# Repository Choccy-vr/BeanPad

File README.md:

# BeanPad

A modular magnetic macro pad. Use many different modules to make the macro pad of your dreams. Modify the macros.json for a custom keymap.

I built this originally as a buffer for my main project but it has since taken over it. The idea came from other snap-fit modular systems and thought it was cool. I originally was just going to make a hack pad but it quickly grew into this.
I also built this in case my other project doesn't get finished in time for undercity.
## Images

### PCB

### Case

### Firmware (Really nothing to see here)

## 
|Item:             |Quanity: (If Items come in sets amount of sets)|Source:                                                                                                                                                                                                                                                                                                                                                                                                                                   |Cost:  |Total                                |
|------------------|-----------------------------------------------|------------------------------------------------------------------------------------------------------------------------------------------------------------------------------------------------------------------------------------------------------------------------------------------------------------------------------------------------------------------------------------------------------------------------------------------|-------|-------------------------------------|
|Screws            |1(50pcs)                                       |https://www.aliexpress.us/item/3256802339245383.html?spm=a2g0o.cart.0.0.7a1938daQ49wN7&mp=1&pdp_npi=5%40dis%21USD%21USD%201.46%21USD%201.41%21%21USD%201.41%21%21%21%402103273e17501073692076879ef915%2112000021000038128%21ct%21US%213108417632%21%211%210&_gl=1*ga8tl1*_gcl_au*NDM2NDExMDYwLjE3NDk1NzAxOTM.*_ga*Nzg5NDk5ODkzLjE3NTAxMDU1ODU.*_ga_VED1YSGNC7*czE3NTAxMDU1ODQkbzEkZzEkdDE3NTAxMDczNzAkajUxJGwwJGgw&gatewayAdapt=glo2usa   |$1.50  |                                     |
|Heat Set Inserts  |1(50pcs)                                       |https://www.aliexpress.us/item/3256807466816961.html?spm=a2g0o.cart.0.0.7a1938daQ49wN7&mp=1&pdp_npi=5%40dis%21USD%21USD%202.02%21USD%201.93%21%21USD%201.93%21%21%21%402103273e17501073692076879ef915%2112000041667111488%21ct%21US%213108417632%21%211%210&_gl=1*ga8tl1*_gcl_au*NDM2NDExMDYwLjE3NDk1NzAxOTM.*_ga*Nzg5NDk5ODkzLjE3NTAxMDU1ODU.*_ga_VED1YSGNC7*czE3NTAxMDU1ODQkbzEkZzEkdDE3NTAxMDczNzAkajUxJGwwJGgw&gatewayAdapt=glo2usa   |$2     |                                     |
|Diodes            |1(100pcs)                                      |https://www.aliexpress.us/item/2255799955957794.html?spm=a2g0o.cart.0.0.7a1938daQ49wN7&mp=1&pdp_npi=5%40dis%21USD%21USD%201.42%21USD%201.42%21%21USD%201.39%21%21%21%402103273e17501073692076879ef915%2110000000428321629%21ct%21US%213108417632%21%211%210&_gl=1*ga8tl1*_gcl_au*NDM2NDExMDYwLjE3NDk1NzAxOTM.*_ga*Nzg5NDk5ODkzLjE3NTAxMDU1ODU.*_ga_VED1YSGNC7*czE3NTAxMDU1ODQkbzEkZzEkdDE3NTAxMDczNzAkajUxJGwwJGgw&gatewayAdapt=glo2usa   |$1     |                                     |
|Cherry MX Switches|1(30pcs)                                       |https://www.aliexpress.us/item/3256806069646359.html?spm=a2g0o.cart.0.0.7a1938daQ49wN7&mp=1&pdp_npi=5%40dis%21USD%21USD%2019.50%21USD%2018.55%21%21USD%2018.55%21%21%21%402103273e17501073692076879ef915%2112000036489552474%21ct%21US%213108417632%21%211%210&_gl=1*xvozit*_gcl_au*NDM2NDExMDYwLjE3NDk1NzAxOTM.*_ga*Nzg5NDk5ODkzLjE3NTAxMDU1ODU.*_ga_VED1YSGNC7*czE3NTAxMDU1ODQkbzEkZzEkdDE3NTAxMDczNzckajQ0JGwwJGgw&gatewayAdapt=glo2usa|$19    |                                     |
|Rotary Encoders   |2                                              |https://www.aliexpress.us/item/3256805010555504.html?spm=a2g0o.cart.0.0.7a1938daQ49wN7&mp=1&pdp_npi=5%40dis%21USD%21USD%201.59%21USD%201.57%21%21USD%201.57%21%21%21%402103273e17501073692076879ef915%2112000032095591035%21ct%21US%213108417632%21%212%210&_gl=1*b3zsk7*_gcl_au*NDM2NDExMDYwLjE3NDk1NzAxOTM.*_ga*Nzg5NDk5ODkzLjE3NTAxMDU1ODU.*_ga_VED1YSGNC7*czE3NTAxMDU1ODQkbzEkZzEkdDE3NTAxMDczNzgkajQzJGwwJGgw&gatewayAdapt=glo2usa   |$3     |                                     |
|KeyCaps           |2(24pcs)                                       |https://www.aliexpress.us/item/3256802719703092.html?spm=a2g0o.cart.0.0.7a1938daQ49wN7&mp=1&pdp_npi=5%40dis%21USD%21USD%204.15%21USD%203.86%21%21USD%203.62%21%21%21%402103273e17501073692076879ef915%2112000025975791590%21ct%21US%213108417632%21%212%210&_gl=1*b3zsk7*_gcl_au*NDM2NDExMDYwLjE3NDk1NzAxOTM.*_ga*Nzg5NDk5ODkzLjE3NTAxMDU1ODU.*_ga_VED1YSGNC7*czE3NTAxMDU1ODQkbzEkZzEkdDE3NTAxMDczNzgkajQzJGwwJGgw&gatewayAdapt=glo2usa   |$7     |                                     |
|Pogo Connectors   |3(9 pairs)                                     |https://www.aliexpress.us/item/3256806345459324.html?spm=a2g0o.detail.0.0.9f08fUkJfUkJyL&mp=1&pdp_npi=5%40dis%21USD%21USD%206.80%21USD%206.80%21%21USD%206.80%21%21%21%402103273e17501073828027372ef915%2112000045728213793%21ct%21US%213108417632%21%213%210&_gl=1*1iabbhw*_gcl_au*NDM2NDExMDYwLjE3NDk1NzAxOTM.*_ga*Nzg5NDk5ODkzLjE3NTAxMDU1ODU.*_ga_VED1YSGNC7*czE3NTAxMDU1ODQkbzEkZzEkdDE3NTAxMDc3MDAkajE2JGwwJGgw&gatewayAdapt=glo2usa|$21    |                                     |
|Soldering Iron    |1                                              |https://www.aliexpress.us/item/3256806823950124.html?spm=a2g0o.cart.0.0.7a1938daQ49wN7&mp=1&pdp_npi=5%40dis%21USD%21USD%2019.24%21USD%207.89%21%21USD%207.89%21%21%21%402103273e17501073692076879ef915%2112000039050811400%21ct%21US%213108417632%21%211%210&_gl=1*y42j40*_gcl_au*NDM2NDExMDYwLjE3NDk1NzAxOTM.*_ga*Nzg5NDk5ODkzLjE3NTAxMDU1ODU.*_ga_VED1YSGNC7*czE3NTAxMDU1ODQkbzEkZzEkdDE3NTAxMDczODEkajQwJGwwJGgw&gatewayAdapt=glo2usa  |$8     |                                     |
|XIAO Rp2040s      |2 (6pcs)                                       |https://www.seeedstudio.com/Seeed-Studio-XIAO-RP2040-3PCS-p-5942.html                                                                                                                                                                                                                                                                                                                                                                     |$27    |                                     |
|PCBs              |4                                              |https://www.pcbway.com/                                                                                                                                                                                                                                                                                                                                                                                                                   |$47.84 |                                     |
|Total             |                                               |                                                                                                                                                                                                                                                                                                                                                                                                                                          |       |$148.23 (Includes Shipping and Taxes)|

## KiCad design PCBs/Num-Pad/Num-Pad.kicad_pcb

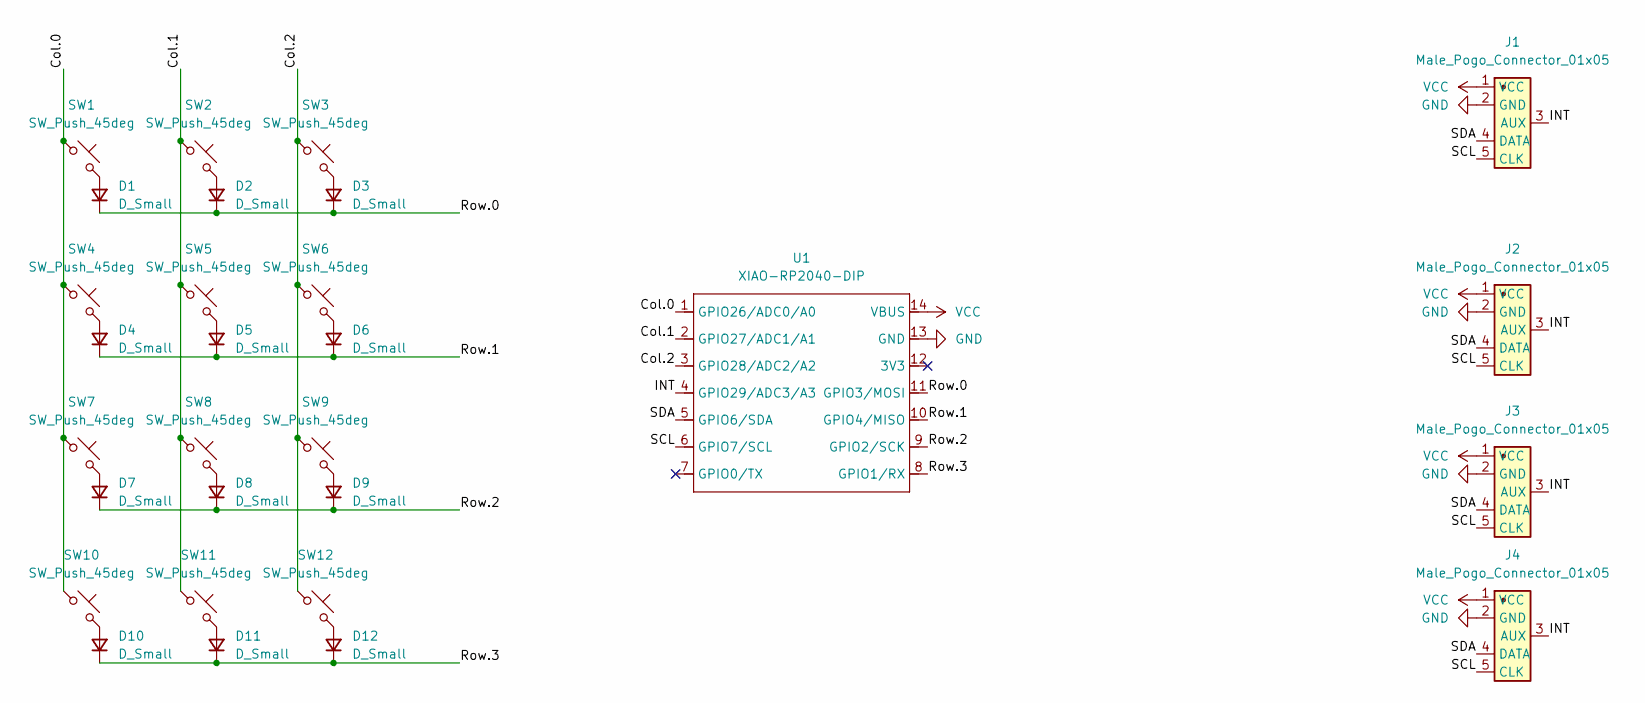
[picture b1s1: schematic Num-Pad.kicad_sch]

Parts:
D1, D2, D3, D4, D5, D6, D7, D8, D9, D10, D11, D12: D_Small; D_DO-35_SOD27_P7.62mm_Horizontal
J1, J2, J3, J4: Male_Pogo_Connector_01x05; PinHeader_1x05_P2.54mm_Vertical
SW1, SW2, SW3, SW4, SW5, SW6, SW7, SW8, SW9, SW10, SW11, SW12: SW_Push_45deg; SW_Cherry_MX_1.00u_PCB
U1: XIAO-RP2040-DIP

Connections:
/Col.0: SW1.1, SW4.1, SW7.1, SW10.1, U1.1 (GPIO26/ADC0/A0)
/Col.1: SW2.1, SW5.1, SW8.1, SW11.1, U1.2 (GPIO27/ADC1/A1)
/Col.2: SW3.1, SW6.1, SW9.1, SW12.1, U1.3 (GPIO28/ADC2/A2)
/INT: J1.3 (AUX), J2.3 (AUX), J3.3 (AUX), J4.3 (AUX), U1.4 (GPIO29/ADC3/A3)
/Row.0: D1.1 (K), D2.1 (K), D3.1 (K), U1.11 (GPIO3/MOSI)
/Row.1: D4.1 (K), D5.1 (K), D6.1 (K), U1.10 (GPIO4/MISO)
/Row.2: D7.1 (K), D8.1 (K), D9.1 (K), U1.9 (GPIO2/SCK)
/Row.3: D10.1 (K), D11.1 (K), D12.1 (K), U1.8 (GPIO1/RX)
/SCL: J1.5 (CLK), J2.5 (CLK), J3.5 (CLK), J4.5 (CLK), U1.6 (GPIO7/SCL)
/SDA: J1.4 (DATA), J2.4 (DATA), J3.4 (DATA), J4.4 (DATA), U1.5 (GPIO6/SDA)
GND: J1.2 (GND), J2.2 (GND), J3.2 (GND), J4.2 (GND), U1.13 (GND)
unnamed: D1.2 (A), SW1.2
unnamed: D2.2 (A), SW2.2
unnamed: D3.2 (A), SW3.2
unnamed: D4.2 (A), SW4.2
unnamed: D5.2 (A), SW5.2
unnamed: D6.2 (A), SW6.2
unnamed: D7.2 (A), SW7.2
unnamed: D8.2 (A), SW8.2
unnamed: D9.2 (A), SW9.2
unnamed: D10.2 (A), SW10.2
unnamed: D11.2 (A), SW11.2
unnamed: D12.2 (A), SW12.2
VCC: J1.1 (VCC), J2.1 (VCC), J3.1 (VCC), J4.1 (VCC), U1.14 (VBUS)

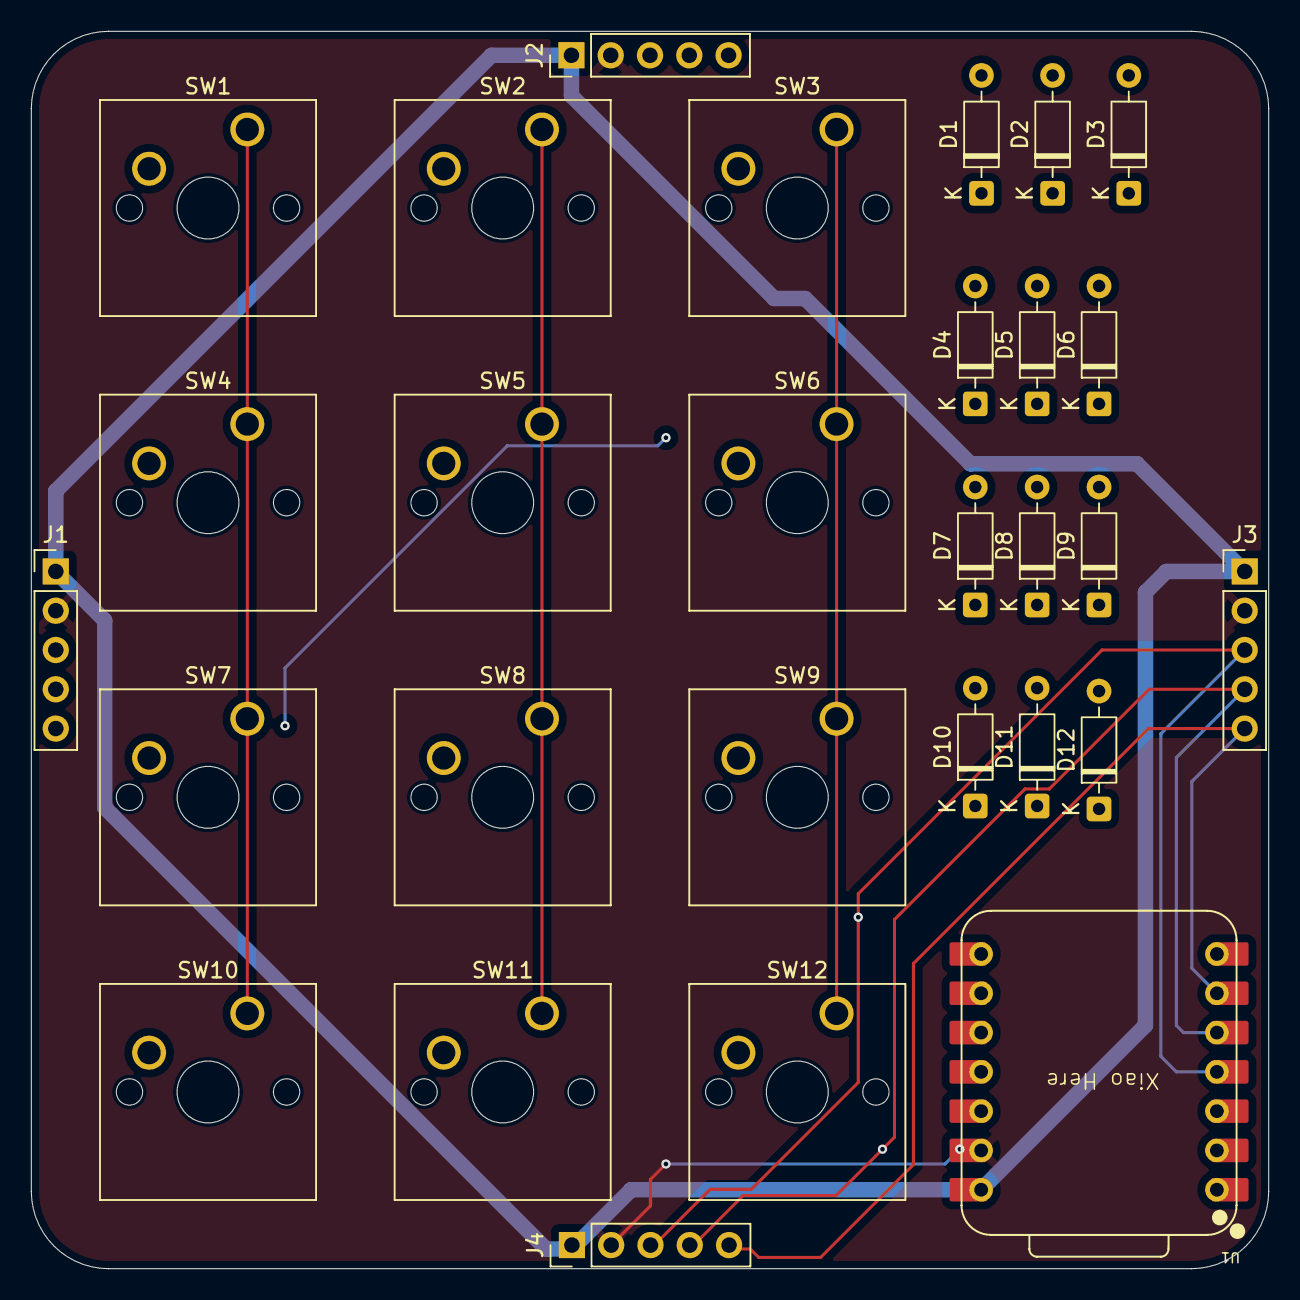
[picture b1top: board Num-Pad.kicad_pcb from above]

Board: 4 copper layers, 80.0 x 80.0 mm, 29 parts (0 on the bottom side), 24 nets.

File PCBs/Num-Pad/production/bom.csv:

Designator,Footprint,Quantity,Value,LCSC Part #
"D1, D10, D11, D12, D2, D3, D4, D5, D6, D7, D8, D9",D_DO-35_SOD27_P7.62mm_Horizontal,12,D_Small,
"J1, J2, J3, J4",PinHeader_1x05_P2.54mm_Vertical,4,Male_Pogo_Connector_01x05,
"SW1, SW10, SW11, SW12, SW2, SW3, SW4, SW5, SW6, SW7, SW8, SW9",SW_Cherry_MX_1.00u_PCB,12,SW_Push_45deg,
U1,XIAO-RP2040-DIP,1,XIAO-RP2040-DIP,

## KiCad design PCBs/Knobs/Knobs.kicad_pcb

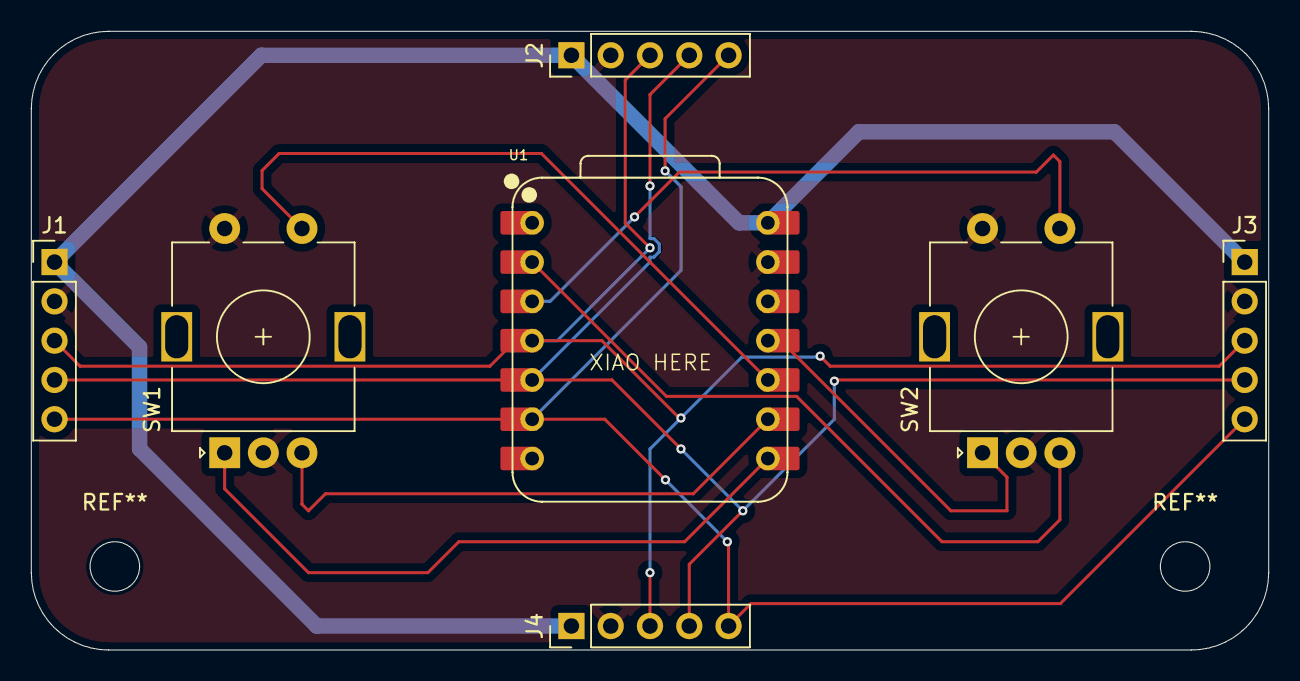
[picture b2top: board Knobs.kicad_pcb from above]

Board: 2 copper layers, 80.0 x 40.0 mm, 7 parts (0 on the bottom side), 11 nets.

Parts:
J1, J2, J3, J4: Male_Pogo_Connector_01x05; PinHeader_1x05_P2.54mm_Vertical
SW1, SW2: RotaryEncoder_Switch; RotaryEncoder_Alps_EC11E-Switch_Vertical_H20mm
U1: XIAO-RP2040-DIP

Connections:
/GPIO1: SW1.A, U1.8 (GPIO1/RX)
/GPIO2: SW1.B, U1.9 (GPIO2/SCK)
/GPIO3: SW2.A, U1.11 (GPIO3/MOSI)
/GPIO4: SW1.S1, U1.10 (GPIO4/MISO)
/GPIO27: SW2.B, U1.2 (GPIO27/ADC1/A1)
/GPIO28: SW2.S1, U1.3 (GPIO28/ADC2/A2)
/INT: J1.3 (AUX), J2.3 (AUX), J3.3 (AUX), J4.3 (AUX), U1.4 (GPIO29/ADC3/A3)
/SCL: J1.5 (CLK), J2.5 (CLK), J3.5 (CLK), J4.5 (CLK), U1.6 (GPIO7/SCL)
/SDA: J1.4 (DATA), J2.4 (DATA), J3.4 (DATA), J4.4 (DATA), U1.5 (GPIO6/SDA)
GND: J1.2 (GND), J2.2 (GND), J3.2 (GND), J4.2 (GND), SW1.C, SW1.S2, SW2.C, SW2.S2, U1.13 (GND)
VCC: J1.1 (VCC), J2.1 (VCC), J3.1 (VCC), J4.1 (VCC), U1.14 (VBUS)

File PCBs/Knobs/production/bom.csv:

Designator,Footprint,Quantity,Value,LCSC Part #
"J1, J2, J3, J4",PinHeader_1x05_P2.54mm_Vertical,4,Male_Pogo_Connector_01x05,
"SW1, SW2",RotaryEncoder_Alps_EC11E-Switch_Vertical_H20mm,2,RotaryEncoder_Switch,
U1,XIAO-RP2040-DIP,1,XIAO-RP2040-DIP,

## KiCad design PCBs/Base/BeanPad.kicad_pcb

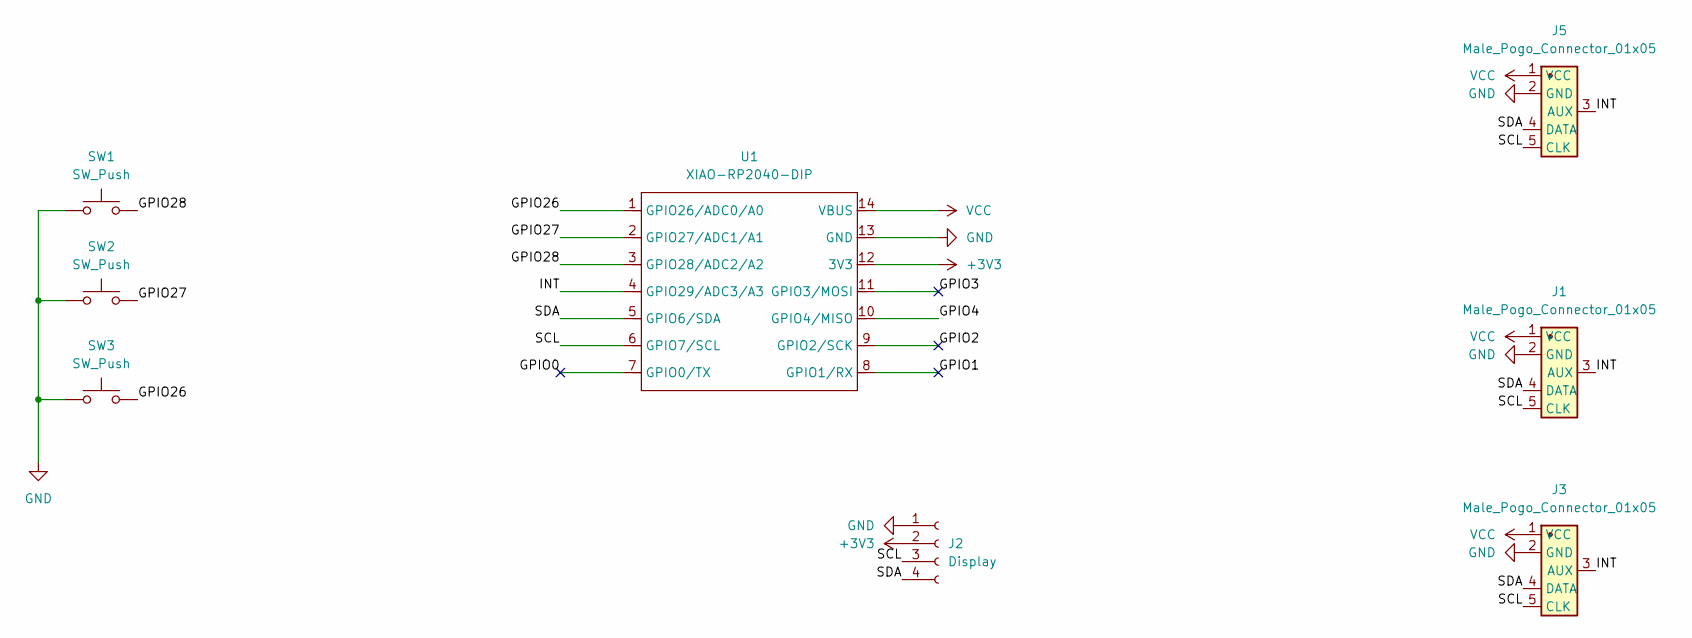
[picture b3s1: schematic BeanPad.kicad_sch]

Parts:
J1, J3, J5: Male_Pogo_Connector_01x05; PinHeader_1x05_P2.54mm_Vertical
J2: Display; SSD1306-0.91-OLED-4pin-128x32
SW1, SW2, SW3: SW_Push; SW_Cherry_MX_1.00u_PCB
U1: XIAO-RP2040-DIP

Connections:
+3V3: J2.2, U1.12 (3V3)
/GPIO0: U1.7 (GPIO0/TX)
/GPIO0_1: U1.7 (GPIO0/TX)
/GPIO1: U1.8 (GPIO1/RX)
/GPIO1_1: U1.8 (GPIO1/RX)
/GPIO2: U1.9 (GPIO2/SCK)
/GPIO2_1: U1.9 (GPIO2/SCK)
/GPIO3: U1.11 (GPIO3/MOSI)
/GPIO3_1: U1.11 (GPIO3/MOSI)
/GPIO4: U1.10 (GPIO4/MISO)
/GPIO26: SW3.2, U1.1 (GPIO26/ADC0/A0)
/GPIO27: SW2.2, U1.2 (GPIO27/ADC1/A1)
/GPIO28: SW1.2, U1.3 (GPIO28/ADC2/A2)
/INT: J1.3 (AUX), J3.3 (AUX), J5.3 (AUX), U1.4 (GPIO29/ADC3/A3)
/SCL: J1.5 (CLK), J2.3, J3.5 (CLK), J5.5 (CLK), U1.6 (GPIO7/SCL)
/SDA: J1.4 (DATA), J2.4, J3.4 (DATA), J5.4 (DATA), U1.5 (GPIO6/SDA)
GND: J1.2 (GND), J2.1, J3.2 (GND), J5.2 (GND), SW1.1, SW2.1, SW3.1, U1.13 (GND)
VCC: J1.1 (VCC), J3.1 (VCC), J5.1 (VCC), U1.14 (VBUS)

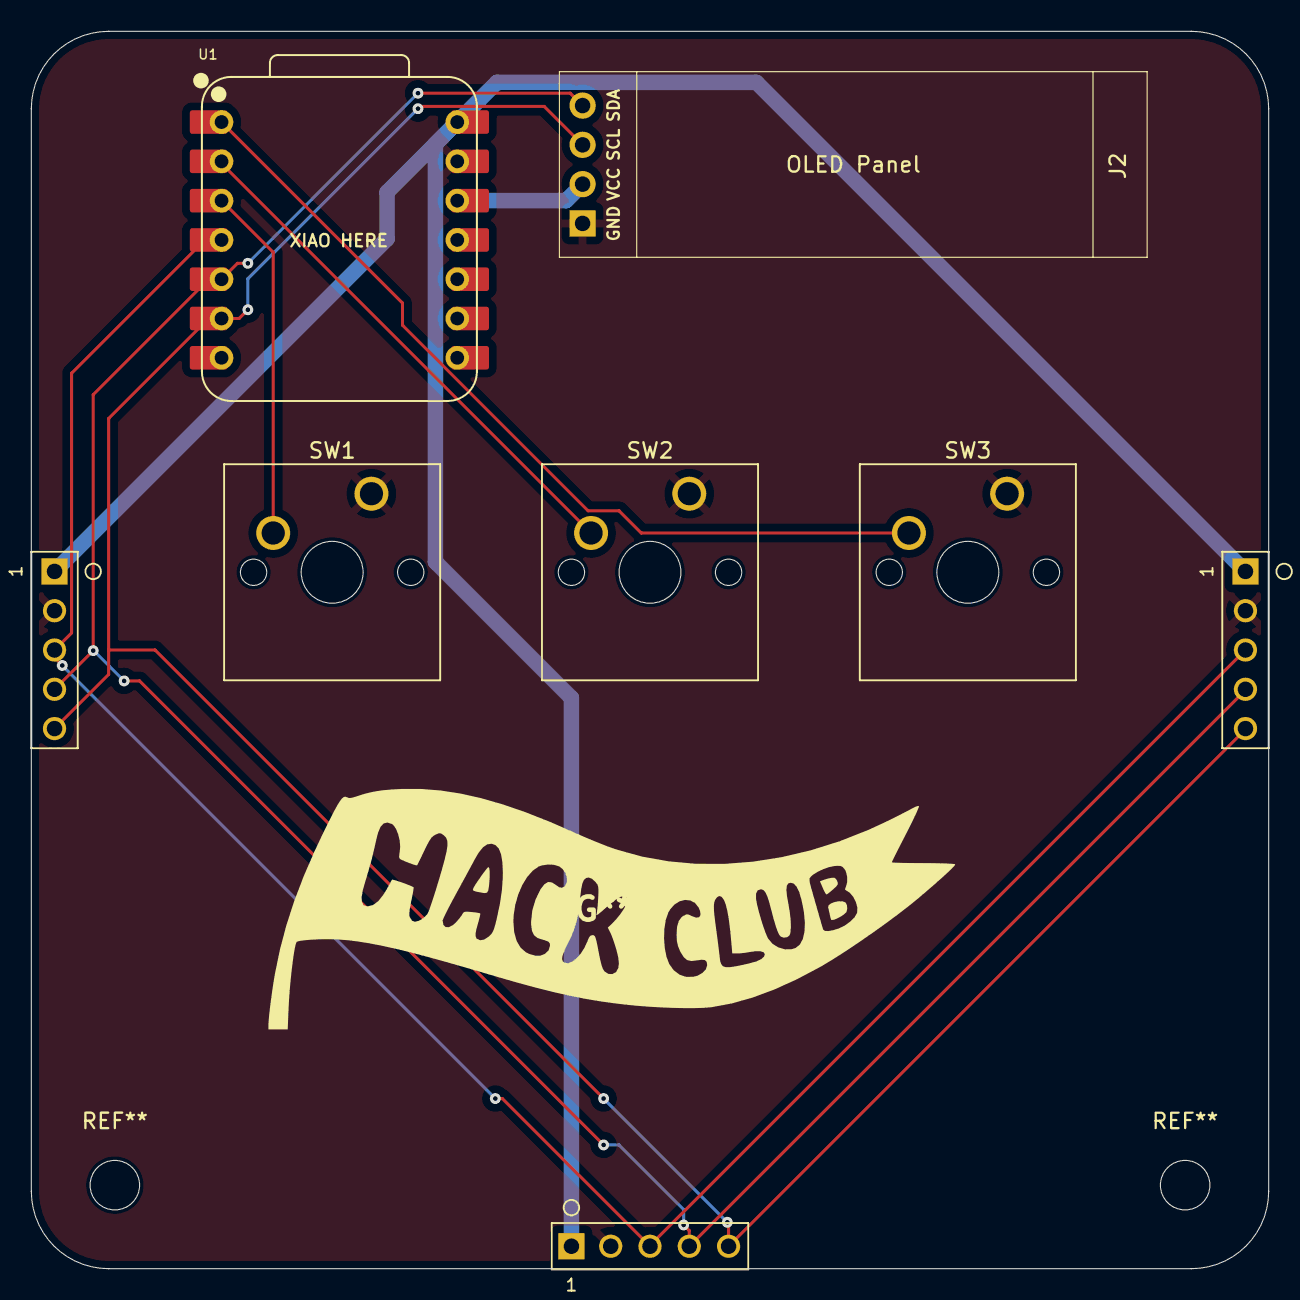
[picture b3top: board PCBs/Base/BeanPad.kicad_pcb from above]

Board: 2 copper layers, 80.0 x 80.0 mm, 8 parts (0 on the bottom side), 9 nets.

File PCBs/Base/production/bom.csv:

Designator,Footprint,Quantity,Value,LCSC Part #
"J1, J3, J5",male_only_connector_5pin_Version3,3,Male_Pogo_Connector_01x05,
J2,SSD1306-0.91-OLED-4pin-128x32,1,Display,
"SW1, SW2, SW3",SW_Cherry_MX_1.00u_PCB,3,SW_Push,
U1,XIAO-RP2040-DIP,1,XIAO-RP2040-DIP,

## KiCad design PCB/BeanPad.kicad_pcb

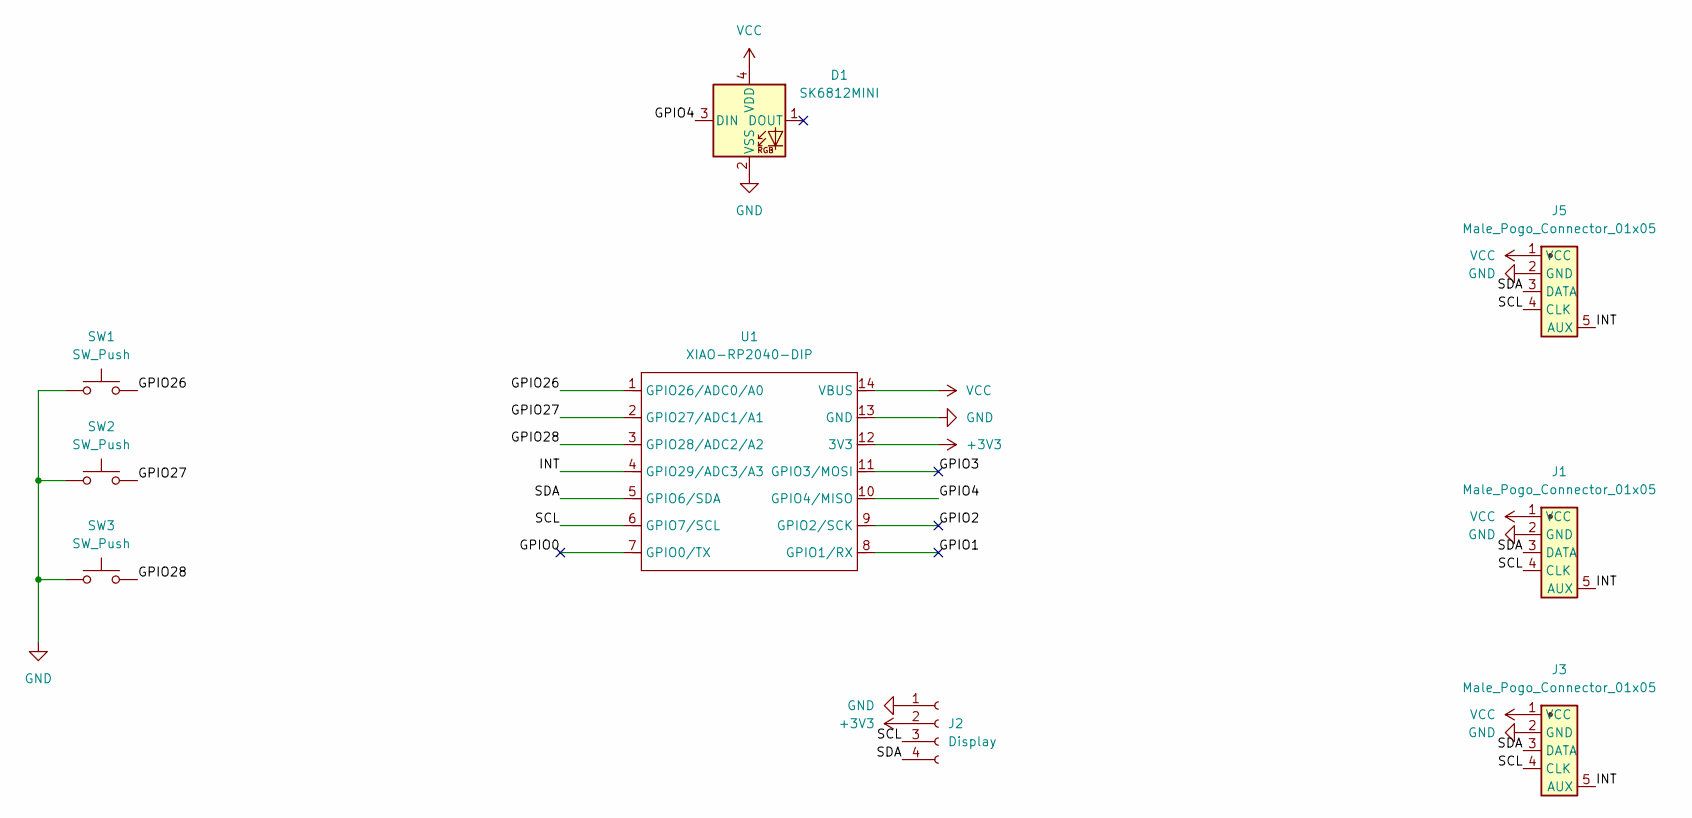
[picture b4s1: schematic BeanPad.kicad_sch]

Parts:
D1: SK6812MINI; LED_SK6812MINI_PLCC4_3.5x3.5mm_P1.75mm
J1, J3, J5: Male_Pogo_Connector_01x05; male_only_connector_5pin_Version3
J2: Display; SSD1306-0.91-OLED-4pin-128x32
SW1, SW2, SW3: SW_Push; SW_Cherry_MX_1.00u_PCB
U1: XIAO-RP2040-DIP

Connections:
+3V3: J2.2, U1.12 (3V3)
/GPIO0: U1.7 (GPIO0/TX)
/GPIO0_1: U1.7 (GPIO0/TX)
/GPIO1: U1.8 (GPIO1/RX)
/GPIO1_1: U1.8 (GPIO1/RX)
/GPIO2: U1.9 (GPIO2/SCK)
/GPIO2_1: U1.9 (GPIO2/SCK)
/GPIO3: U1.11 (GPIO3/MOSI)
/GPIO3_1: U1.11 (GPIO3/MOSI)
/GPIO4: D1.3 (DIN), U1.10 (GPIO4/MISO)
/GPIO26: SW1.2, U1.1 (GPIO26/ADC0/A0)
/GPIO27: SW2.2, U1.2 (GPIO27/ADC1/A1)
/GPIO28: SW3.2, U1.3 (GPIO28/ADC2/A2)
/INT: J1.5 (AUX), J3.5 (AUX), J5.5 (AUX), U1.4 (GPIO29/ADC3/A3)
/SCL: J1.4 (CLK), J2.3, J3.4 (CLK), J5.4 (CLK), U1.6 (GPIO7/SCL)
/SDA: J1.3 (DATA), J2.4, J3.3 (DATA), J5.3 (DATA), U1.5 (GPIO6/SDA)
GND: D1.2 (VSS), J1.2 (GND), J2.1, J3.2 (GND), J5.2 (GND), SW1.1, SW2.1, SW3.1, U1.13 (GND)
VCC: D1.4 (VDD), J1.1 (VCC), J3.1 (VCC), J5.1 (VCC), U1.14 (VBUS)

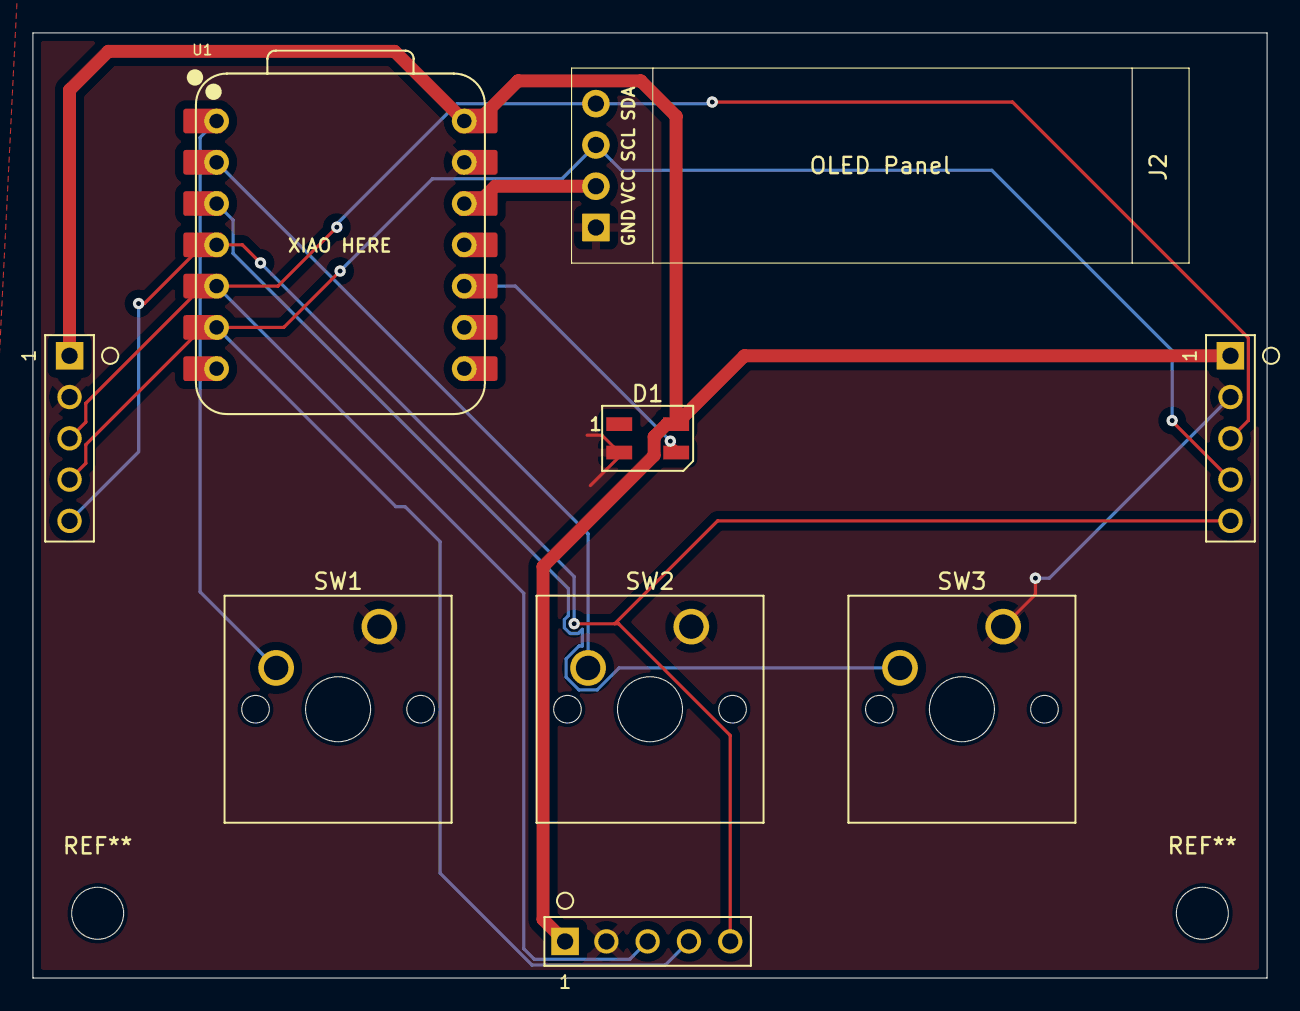
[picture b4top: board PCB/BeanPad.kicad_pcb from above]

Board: 2 copper layers, 75.9 x 58.2 mm, 9 parts (0 on the bottom side), 10 nets.

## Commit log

2025-06-09 PCB V1.0 Schematic
2025-06-10 PCB finished v1
2025-06-10 Case and edit PCB
2025-06-11 Case V0.1 done
2025-06-13 Firmware
2025-06-15 Modules
2025-06-15 Almost Completed Module
2025-06-16 Finished Designing
2025-06-16 Fix a few things
2025-06-19 Modify
2025-06-19 Fix Macro Module CAD
2025-06-19 Fix PCB and Pictures
2025-09-07 Refactor I2C module handling and update PCB files
    Major refactor of I2C communication between the main board and modules: unified pin naming, improved interrupt and keymap handling, and enhanced display logic in the main firmware. Updated PCB projec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
